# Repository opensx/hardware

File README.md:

# hardware
Design Files für die OpenSX Hardware, siehe <a href="http://opensx.net"> opensx.net </a>

Insgesamt soll mit den Projekten von "OpenSX" ein kompletter Modellbahnbetrieb möglich 
sein - die Bausteine können aber auch mit allen Standard Selectrix Modulen und Zentralen 
verwendet werden, sie sind "SX1-kompatibel".

Die Projekte auf diese Seite beruhen auf "Open Source" Software, aber auch auf 
"Open Source Hardware". Sie können also von jedem/jeder nachgebaut werden. 
Wir sind der Meinung, dass jeder/jeder die Möglichkeit haben sollte, die Hardware und 
auch die Software zu verstehen, sie ändern können sollte (und verbesssern) und auch 
diese Änderungen weitergeben sollte.

Dazu werden nach und nach nebem dem Source Code (lizensiert nach <a href="http://www.gnu.org/licenses/gpl-3.0.de.html">GPLv3</a>), 
der auch hier liegt, auch die Schaltpläne und Eagle Design Files veröffentlicht. 
Sie sind lizensiert unter der <a href="https://creativecommons.org/licenses/by-sa/4.0/de">"Creative Commons Attribution Share-Alike" Lizenz</a> - 
die eine persönliche und kommerzielle Weiterverwertung erlaubt, solange in angemesse Weise
die Urheberschaft von "opensx" erwähnt wird und die abgeleitete Arbeit unter der gleichen 
Lizenz steht. (dies ist die gleiche Lizenz wie beim Arduino Projekt)

<br />This work is licensed under a <a rel="license" href="http://creativecommons.org/licenses/by-sa/4.0/">Creative Commons Attribution-ShareAlike 4.0 International License</a>.

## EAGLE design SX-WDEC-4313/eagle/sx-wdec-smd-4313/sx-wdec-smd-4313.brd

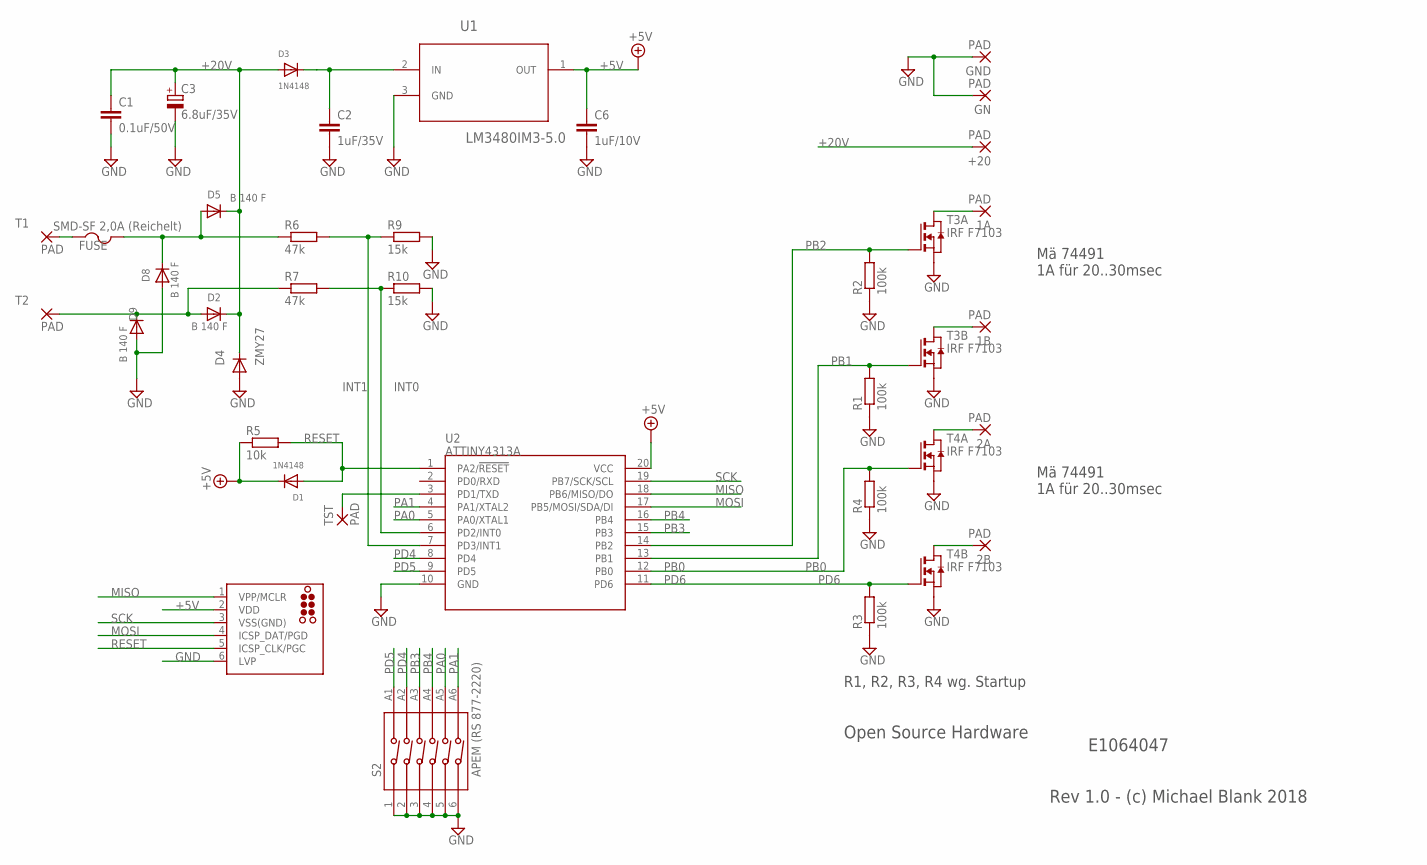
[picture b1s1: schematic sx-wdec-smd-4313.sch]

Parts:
1A, 1B, 2A, 2B: PAD; SMD1,27-2,54
+20: PAD; SMD1,27-2,54
C1: 0.1uF/50V; C0805
C2: 1uF/35V; C0805
C3: 6.8uF/35V; SMC_D
C6: 1uF/10V; C0805
D1, D3: 1N4148; SOD-323F
D2, D5, D8, D9: B 140 F; SMA-403D
D4: ZMY27; MELF-MLL41
FUSE: SMD-SF 2,0A (Reichelt); 1812
GN: PAD; SMD1,27-2,54
GND: PAD; SMD1,27-2,54
J1: ISP; TC2030-MCP-NL
R1, R2, R3, R4: 100k; R0805W
R5: 10k; R0805W
R6, R7: 47k; R0805W
R9, R10: 15k; R0805W
S2: APEM (RS 877-2220); 416131160806
T1, T2: PAD; SMD1,27-2,54
T3, T4: IRF F7103; SO8
TST: PAD; SMD1,27-2,54
U1: LM3480IM3-5.0; SOT95P263X110-3N
U2: ATTINY4313A; SOP20W

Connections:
+5V: C6.1, D1.C, J1.2 (VDD), R5.1, U1.1 (OUT), U2.20 (VCC)
+20V: +20.1, C1.1, C3.+, D2.C, D3.A, D4.C, D5.C
GND: C1.2, C2.2, C3.-, C6.2, D4.A, D8.A, D9.A, GN.1, GND.1, J1.6 (LVP), R1.1, R2.1, R3.1, R4.1, R9.2, R10.2, S2.1, S2.2, S2.3, S2.4, S2.5, S2.6, T3.1 (S), T3.3 (S), T4.1 (S), T4.3 (S), U1.3 (GND), U2.10 (GND)
INT0: R7.2, R10.1, U2.6 (PD2/INT0)
INT1: R6.2, R9.1, U2.7 (PD3/INT1)
MISO: J1.1 (VPP/MCLR), U2.18 (PB6/MISO/DO)
MOSI: J1.4 (ICSP_DAT/PGD), U2.17 (PB5/MOSI/SDA/DI)
unnamed: 2B.1, T4.5 (D), T4.6 (D)
unnamed: 2A.1, T4.7 (D), T4.8 (D)
unnamed: FUSE.1, T1.1
unnamed: D5.A, D8.C, FUSE.2, R6.1
unnamed: TST.1, U2.3 (PD1/TXD)
unnamed: C2.1, D3.C, U1.2 (IN)
unnamed: 1B.1, T3.5 (D), T3.6 (D)
unnamed: 1A.1, T3.7 (D), T3.8 (D)
PA0: S2.A5, U2.5 (PA0/XTAL1)
PA1: S2.A6, U2.4 (PA1/XTAL2)
PB0: R4.2, T4.2 (G), U2.12 (PB0)
PB1: R1.2, T3.4 (G), U2.13 (PB1)
PB2: R2.2, T3.2 (G), U2.14 (PB2)
PB3: S2.A3, U2.15 (PB3)
PB4: S2.A4, U2.16 (PB4)
PD4: S2.A2, U2.8 (PD4)
PD5: S2.A1, U2.9 (PD5)
PD6: R3.2, T4.4 (G), U2.11 (PD6)
RESET: D1.A, J1.5 (ICSP_CLK/PGC), R5.2, U2.1 (PA2/!RESET)
SCK: J1.3 (VSS(GND)), U2.19 (PB7/SCK/SCL)
TR-L: D2.A, D9.C, R7.1, T2.1

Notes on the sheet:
Mä 74491 1A für 20..30msec
R1, R2, R3, R4 wg. Startup
Open Source Hardware
Rev 1.0 - (c) Michael Blank 2018
E1064047

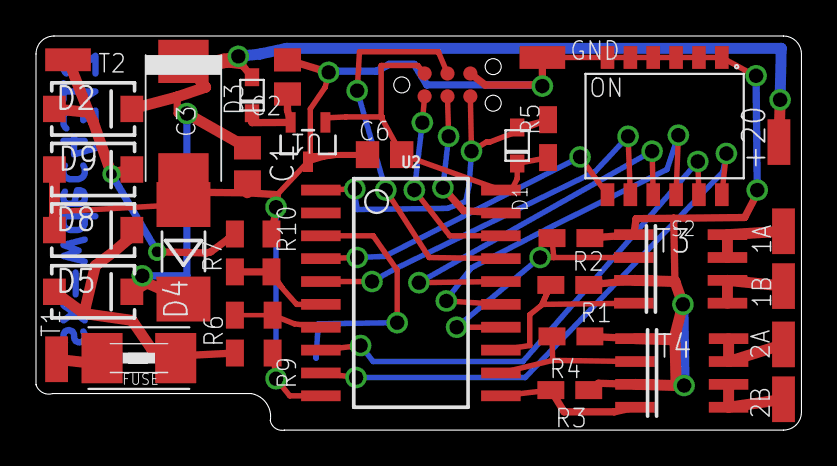
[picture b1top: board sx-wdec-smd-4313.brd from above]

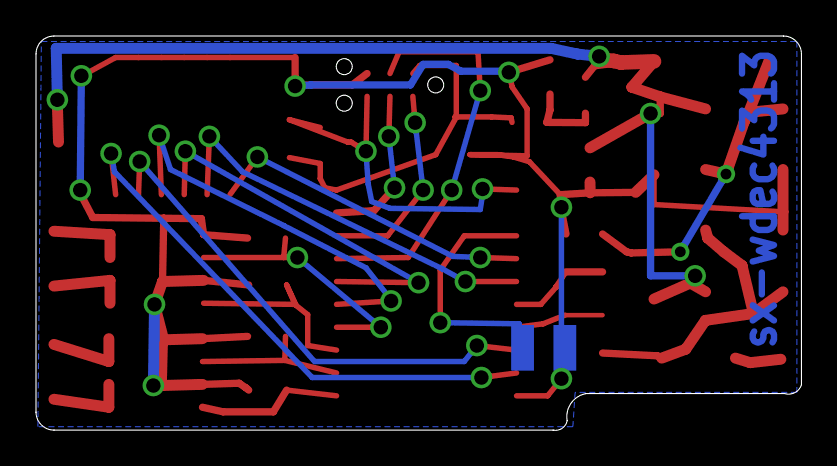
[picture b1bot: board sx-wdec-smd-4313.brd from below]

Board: 2 copper layers, 42.5 x 21.9 mm, 37 parts (2 on the bottom side), 28 nets.

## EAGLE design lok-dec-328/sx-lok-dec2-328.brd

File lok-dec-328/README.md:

# Arduino Lok-Decoder mit ATmega328
Design Files für die OpenSX Hardware, siehe <a href="http://opensx.net"> opensx.net </a>

Rev. 3, siehe sx-lok-dec3.sch.pdf : hier wurden 2 Widerstände an den Eingängen D2 und D3 nach Masse hinzugefügt - nur für Selectrix benötigt, da sonst die "0" Spannung nicht immer richtig erkannt wird.

lizensiert nach <a href="http://www.gnu.org/licenses/gpl-3.0.de.html">GPLv3</a>)

Sie sind lizensiert unter der <a href="https://creativecommons.org/licenses/by-sa/4.0/de">"Creative Commons Attribution Share-Alike" Lizenz</a> - 
die eine persönliche und kommerzielle Weiterverwertung erlaubt, solange in angemesse Weise
die Urheberschaft von "opensx" erwähnt wird und die abgeleitete Arbeit unter der gleichen 
Lizenz steht. (dies ist die gleiche Lizenz wie beim Arduino Projekt)

<br />This work is licensed under a <a rel="license" href="http://creativecommons.org/licenses/by-sa/4.0/">Creative Commons Attribution-ShareAlike 4.0 International License</a>.

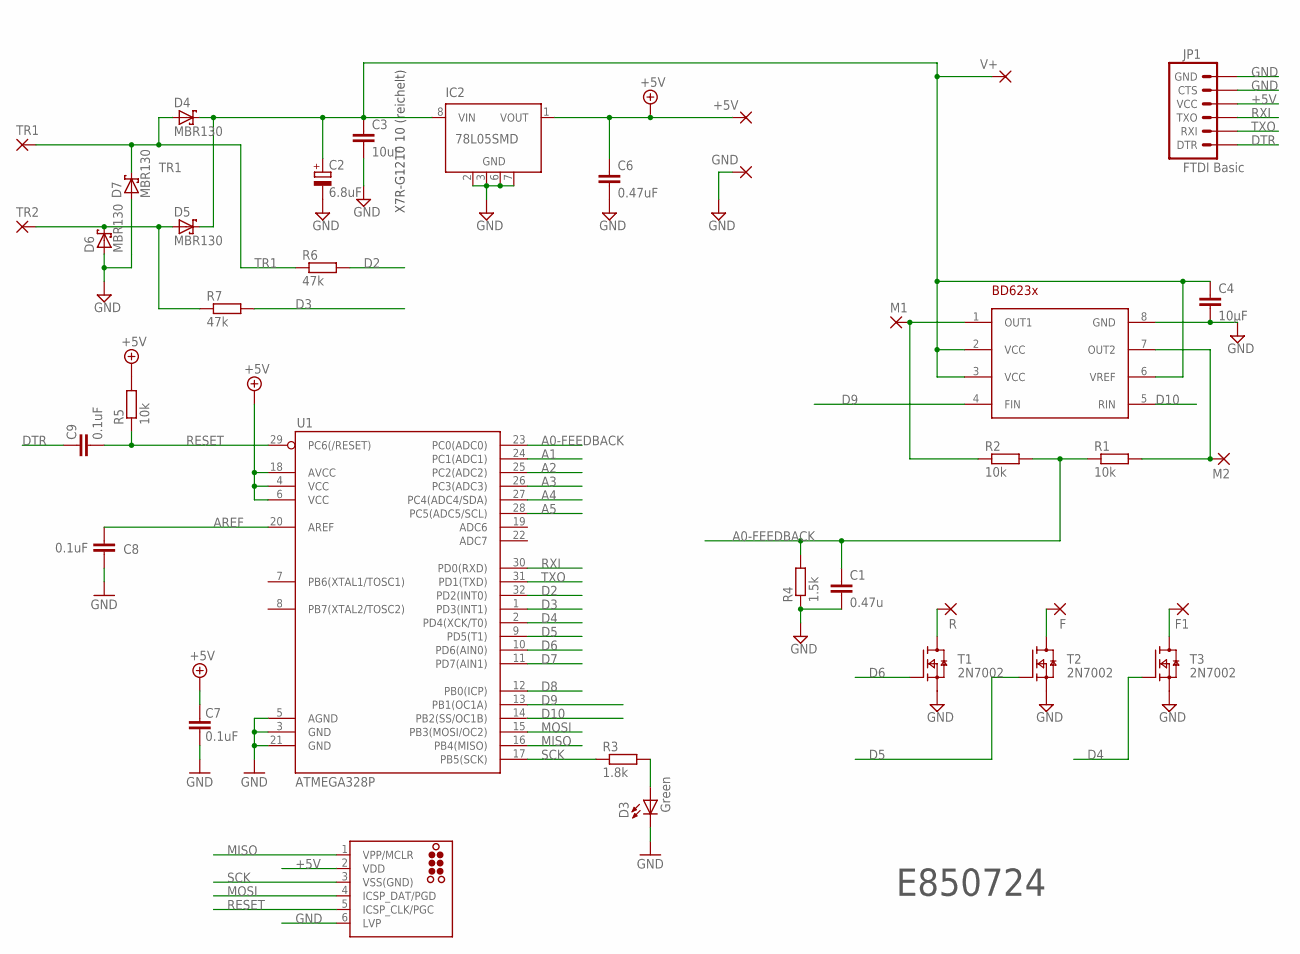
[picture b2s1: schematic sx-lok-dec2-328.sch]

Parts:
+5V: SMD2; SMD1,27-2,54
BD6231: BD6231F; SOP8
C1: 0.47u; C1206
C2: 6.8uF; SMC_D
C3: 10uF; C0805K
C4: 10µF; C1210K
C6: 0.47uF; C1206
C7, C8, C9: 0.1uF; 0805
D3: Green; LED-0603
D4, D5, D6, D7: MBR130; SOD123F
F, F1: SMD2; SMD1,27-2,54
GND: SMD2; SMD1,27-2,54
IC2: 78L05SMD; SO08
J1: ISP; TC2030-MCP-NL
JP1: FTDI Basic; 1X06
M1, M2: SMD2; SMD1,27-2,54
R: SMD2; SMD1,27-2,54
R1, R2: 10k; R0805
R3: 1.8k; M0805
R4: 1.5k; R0805
R5: 10k; M0805
R6: 47k; R0805
R7: 47k; M0805
T1, T2, T3: 2N7002; SOT23
TR1, TR2: SMD2; SMD1,27-2,54
U1: ATMEGA328P; TQFP32-08
V+: SMD2; SMD1,27-2,54

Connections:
+5V: +5V.1, C6.1, C7.2, IC2.1 (VOUT), J1.2 (VDD), JP1.4 (VCC), R5.2, U1.4 (VCC), U1.6 (VCC), U1.18 (AVCC)
+20V: BD6231.2 (VCC), BD6231.3 (VCC), BD6231.6 (VREF), C2.+, C3.1, C4.1, D4.1 (K), D5.1 (K), IC2.8 (VIN), V+.1
A0-FEEDBACK: C1.1, R1.1, R2.2, R4.2, U1.23 (PC0(ADC0))
A1: U1.24 (PC1(ADC1))
A2: U1.25 (PC2(ADC2))
A3: U1.26 (PC3(ADC3))
A4: U1.27 (PC4(ADC4/SDA))
A5: U1.28 (PC5(ADC5/SCL))
AREF: C8.2, U1.20 (AREF)
D2: R6.2, U1.32 (PD2(INT0))
D3: R7.2, U1.1 (PD3(INT1))
D4: T3.1 (G), U1.2 (PD4(XCK/T0))
D5: T2.1 (G), U1.9 (PD5(T1))
D6: T1.1 (G), U1.10 (PD6(AIN0))
D7: U1.11 (PD7(AIN1))
D8: U1.12 (PB0(ICP))
D9: BD6231.4 (FIN), U1.13 (PB1(OC1A))
D10: BD6231.5 (RIN), U1.14 (PB2(SS/OC1B))
DTR: C9.2, JP1.1 (DTR)
GND: BD6231.8 (GND), C1.2, C2.-, C3.2, C4.2, C6.2, C7.1, C8.1, D3.C, D6.2 (A), D7.2 (A), GND.1, IC2.2 (GND), IC2.3 (GND), IC2.6 (GND), IC2.7 (GND), J1.6 (LVP), JP1.5 (CTS), JP1.6 (GND), R4.1, T1.2 (S), T2.2 (S), T3.2 (S), U1.3 (GND), U1.5 (AGND), U1.21 (GND)
MISO: J1.1 (VPP/MCLR), U1.16 (PB4(MISO))
MOSI: J1.4 (ICSP_DAT/PGD), U1.15 (PB3(MOSI/OC2))
MOTOR1: BD6231.1 (OUT1), M1.1, R2.1
MOTOR2: BD6231.7 (OUT2), M2.1, R1.2
unnamed: D3.A, R3.2
unnamed: R.1, T1.3 (D)
unnamed: F.1, T2.3 (D)
unnamed: F1.1, T3.3 (D)
RESET: C9.1, J1.5 (ICSP_CLK/PGC), R5.1, U1.29 (PC6(/RESET))
RXI: JP1.3 (TXO), U1.30 (PD0(RXD))
SCK: J1.3 (VSS(GND)), R3.1, U1.17 (PB5(SCK))
TR1: D4.2 (A), D7.1 (K), R6.1, TR1.1
TR-L1: D5.2 (A), D6.1 (K), R7.1, TR2.1
TXO: JP1.2 (RXI), U1.31 (PD1(TXD))

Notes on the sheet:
X7R-G1210 10 (reichelt)
E850724

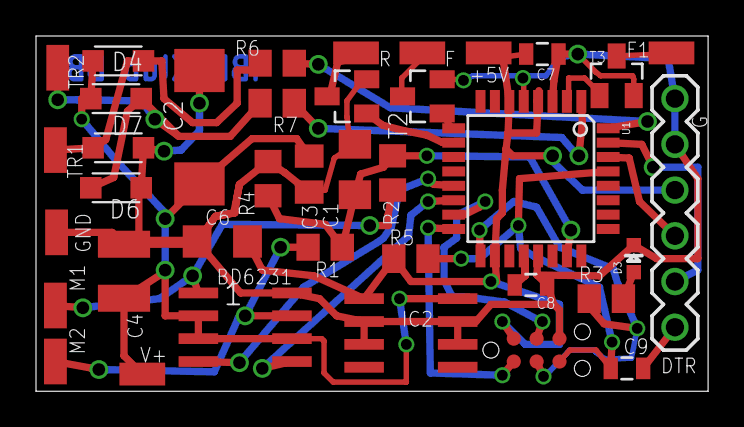
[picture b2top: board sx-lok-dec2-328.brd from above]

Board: 2 copper layers, 37.3 x 19.7 mm, 38 parts (0 on the bottom side), 27 nets.

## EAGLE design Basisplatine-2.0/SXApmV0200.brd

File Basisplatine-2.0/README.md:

# Basisplatine 2.0 mit DIN Buchsen

siehe <a href="http://opensx.net/projekte/basisplatine/neue-version-v02-00/"> OpenSX Basisplatine Version 2.00 mit DIN Buchsen</a> - hierzu muss die Arduino Lib SX30 verwendet werden, siehe  <a href="https://github.com/opensx/SX30/"> SX Library mit Beispiel "Belegtmelder" </a>.

Auf die Basisplatine kann zB eine Belegtmelderplatine aufgesetzt werden:

<br />This work is licensed under a <a rel="license" href="http://creativecommons.org/licenses/by-sa/4.0/">Creative Commons Attribution-ShareAlike 4.0 International License</a>.

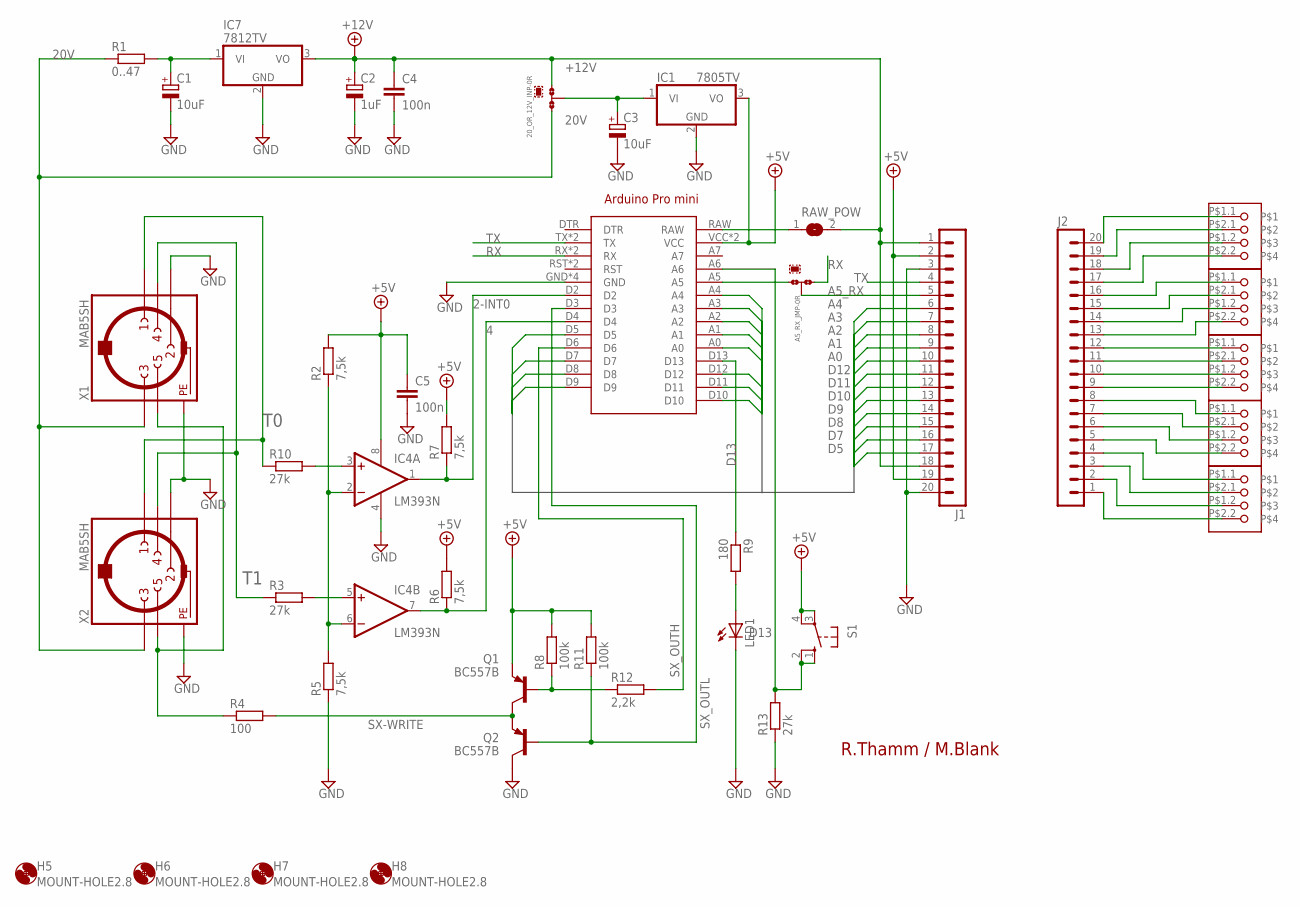
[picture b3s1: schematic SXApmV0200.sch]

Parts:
20_OR_12V_INP: 0R-JUMPA; A0R-JMP
A5_RX_JMP: 0R-JUMPB; B0R-JMP
ARDUINO1: ARDUINO_PRO_MINI
C1: 10uF; E2,5-7
C2: 1uF; E2,5-7
C3: 10uF; SMC_C
C4, C5: 100n; C050-025X075
H5, H6, H7, H8: MOUNT-HOLE2.8; 2,8
IC1: 7805TV; TO220V
IC4: LM393N; DIL08
IC7: 7812TV; TO220V
J1, J2: MA20-1
LED1: LED3MM
Q1, Q2: BC557B; TO92-EBC
R1: 0..47; 0207/12
R2, R5, R6, R7: 7,5k; 0207/10
R3, R10, R13: 27k; 0207/10
R4: 100; 0207/10
R8, R11: 100k; 0207/10
R9: 180; 0207/2V
R12: 2,2k; 0207/10
RAW_POW: SJ
S1: 10-XX; B3F-10XX
U$1, U$2, U$3, U$4, U$5: AKL093-06
X1, X2: MAB5SH

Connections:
2-INT0: ARDUINO1.D2, IC4.1 (OUT), R7.1
4: ARDUINO1.D4, IC4.7 (OUT), R6.1
20V: 20_OR_12V_INP.3, R1.1, X1.3, X2.3
+5V: ARDUINO1.VCC, ARDUINO1.VCC@1 (VCC), C5.1, IC1.3 (VO), IC4.8 (V+), J1.2, J1.19, Q1.E, R2.2, R6.2, R7.2, R8.2, R11.2, S1.3, S1.4 (P1)
+12V: 20_OR_12V_INP.1, C2.+, C4.1, IC7.3 (VO), J1.1, J1.18, RAW_POW.2
A0: ARDUINO1.A0, J1.10
A1: ARDUINO1.A1, J1.9
A2: ARDUINO1.A2, J1.8
A3: ARDUINO1.A3, J1.7
A4: ARDUINO1.A4, J1.6
A5: A5_RX_JMP.3, ARDUINO1.A5
A5_RX: A5_RX_JMP.2, J1.5
D5: ARDUINO1.D5, J1.17
D7: ARDUINO1.D7, J1.16
D8: ARDUINO1.D8, J1.15
D9: ARDUINO1.D9, J1.14
D10: ARDUINO1.D10, J1.13
D11: ARDUINO1.D11, J1.12
D12: ARDUINO1.D12, J1.11
D13: ARDUINO1.D13, R9.1
GND: ARDUINO1.GND, ARDUINO1.GND@1 (GND), ARDUINO1.GND@2 (GND), ARDUINO1.GND@3 (GND), C1.-, C2.-, C3.-, C4.2, C5.2, IC1.2 (GND), IC4.4 (V-), IC7.2 (GND), J1.3, J1.20, LED1.K (C), Q2.C, R5.1, R13.1, X1.2, X1.PE, X1.PE@ (PE), X1.PE@1 (PE), X1.PE@2 (PE), X2.2, X2.PE, X2.PE@ (PE), X2.PE@1 (PE), X2.PE@2 (PE)
unnamed: LED1.A, R9.2
unnamed: C1.+, IC7.1 (VI), R1.2
unnamed: R4.1, X1.5, X2.5
unnamed: IC4.3 (+IN), R10.2
unnamed: IC4.5 (+IN), R3.2
unnamed: J2.1, U$4.P$2.2
unnamed: IC4.2 (-IN), IC4.6 (-IN), R2.1, R5.2
unnamed: J2.2, U$4.P$1.2
unnamed: J2.3, U$4.P$2.1
unnamed: J2.4, U$4.P$1.1
unnamed: J2.5, U$3.P$2.2
unnamed: J2.6, U$3.P$1.2
unnamed: J2.7, U$3.P$2.1
unnamed: J2.8, U$3.P$1.1
unnamed: J2.9, U$1.P$2.2
unnamed: J2.10, U$1.P$1.2
unnamed: J2.11, U$1.P$2.1
unnamed: J2.12, U$1.P$1.1
unnamed: J2.13, U$2.P$2.2
unnamed: J2.14, U$2.P$1.2
unnamed: J2.15, U$2.P$2.1
unnamed: J2.16, U$2.P$1.1
unnamed: J2.17, U$5.P$2.2
unnamed: J2.18, U$5.P$1.2
unnamed: J2.19, U$5.P$2.1
unnamed: J2.20, U$5.P$1.1
unnamed: ARDUINO1.A6, R13.2, S1.1 (S), S1.2 (S1)
unnamed: Q1.B, R8.1, R12.1
unnamed: ARDUINO1.RAW, RAW_POW.1
unnamed: 20_OR_12V_INP.2, C3.+, IC1.1 (VI)
RX: A5_RX_JMP.1, ARDUINO1.RX, ARDUINO1.RX@1 (RX)
SX-WRITE: Q1.C, Q2.E, R4.2
SX_OUTH: ARDUINO1.D6, R12.2
SX_OUTL: ARDUINO1.D3, Q2.B, R11.1
T0: R10.1, X1.1, X2.1
T1: R3.1, X1.4, X2.4
TX: ARDUINO1.TX, ARDUINO1.TX@1 (TX), J1.4

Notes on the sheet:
R.Thamm / M.Blank

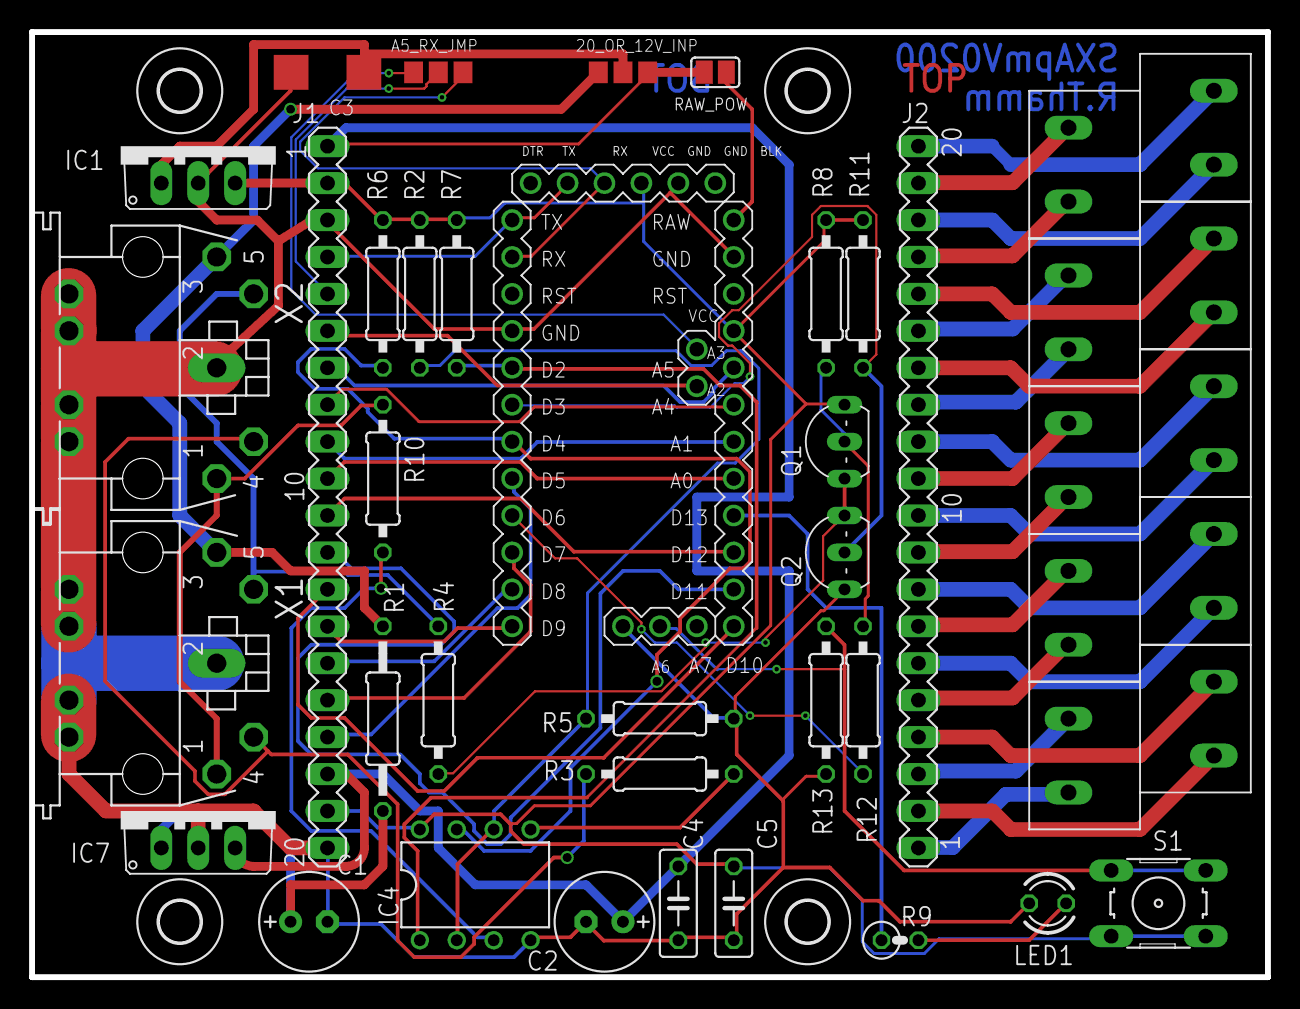
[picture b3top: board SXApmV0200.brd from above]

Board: 2 copper layers, 85.0 x 65.0 mm, 42 parts (0 on the bottom side), 58 nets.

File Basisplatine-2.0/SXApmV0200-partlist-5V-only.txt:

Partlist

Exported from SXApmV0200.sch at 16.09.16 17:11

Assembly variant: 5V-only !

Part           Value          Package          

20_OR_12V_INP  Jumper in Stellung "20" (der 5V Regler wird direkt aus den 20V vom Bus gespeist)
A5_RX_JMP      nicht gesetzt (=offen)
ARDUINO1       ARDUINO_PRO_MINI (5V Version)
C1             nicht bestückt
C2             nicht bestückt
C3             10uF / 35V (nicht notwendig, wenn 5V Schaltregler verwendet wird)
C4             nicht bestückt
C5             100n (Keramik Cap.)  
IC1            TSR 0.5-2450 (Reichelt, Traco, 5V Schaltregler, 500mA)       
IC4            LM393N         DIL08                    
IC7            nicht bestückt !           
J1             MA20-1        Buchsenleiste 20 polig, 2.54mm Raster, 8.5mm hoch
                             (zum Beispiel Reichelt BL 1X20G8 2,54 )
J2             MA20-1        Buchsenleiste 20 polig, 2.54mm Raster, 8.5mm hoch
LED1           LED3MM        (rot oder grün)
Q1             BC557B         TO92-EBC         transistor-pnp     
Q2             BC557B         TO92-EBC         transistor-pnp    
R1             nicht bestückt
R2             7,5k           R-EU_0207/10     
R3             27k            R-EU_0207/10     
R4             100            R-EU_0207/10     
R5             7,5k           R-EU_0207/10     
R6             7,5k           R-EU_0207/10     
R7             7,5k           R-EU_0207/10     
R8             100k           R-EU_0207/10     
R9             180 (bzw 1.8k, wenn die LED1 vom Typ "low current" (2mA) ist)       
R10            27k            R-EU_0207/10     
R11            100k           R-EU_0207/10     
R12            2,2k           R-EU_0207/10     
R13            27k            R-EU_0207/10     
RAW_POW        nicht gesetzt (=offen)           1
S1             Kurzhubtaster 6x6mm (z.B. Reichelt TASTER 3301)
U$1..U$5       Nur die vorderen 10 Kontakte werden genutzt (RM 5,08)
                      (zum Beispiel Reichelt - AKL 101-10)
X1             DIN-Buchse, 5polig (zB Reichelt MABP 5S oder Reichelt MABPM 5S )
X2             DIN-Buchse, 5polig (zB Reichelt MABP 5S oder Reichelt MABPM 5S )

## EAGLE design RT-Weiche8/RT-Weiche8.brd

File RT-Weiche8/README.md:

# "RT-Weiche8" Add-on Platine (für eine der SX- oder LocoNet- Basisplatinen) 

Sie ermöglicht das Ansteuern von 8 Tortoise Antrieben (mit LB1909MC Treibern).

Für die Weichenmotoren ist eine separate Spannung vorgesehen (IC1), sie kann zum Beispiel 9V oder 12V betragen.

Modul-Gehäuse: Strapubox 523 (strapubox.de)

<br />This work is licensed under a <a rel="license" href="http://creativecommons.org/licenses/by-sa/4.0/">Creative Commons Attribution-ShareAlike 4.0 International License</a>.

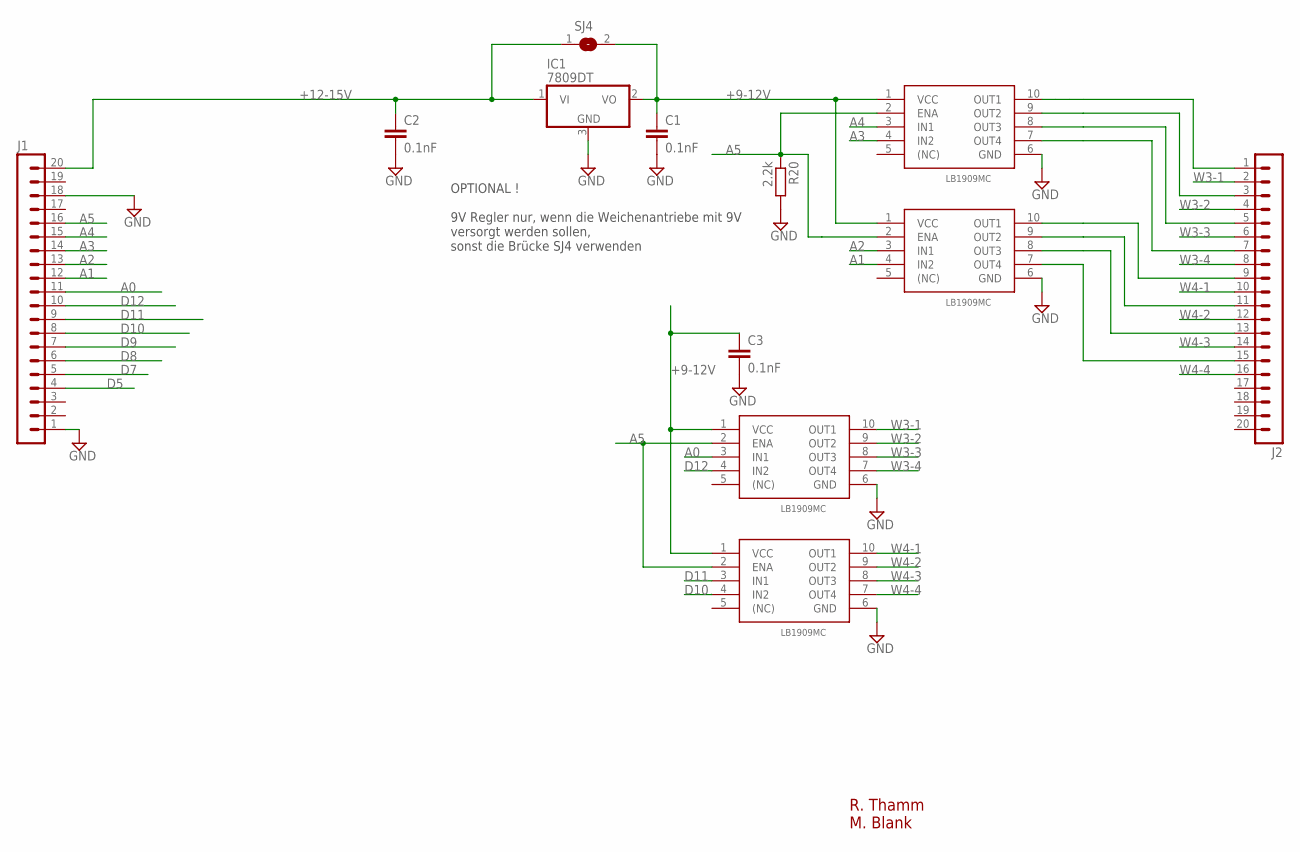
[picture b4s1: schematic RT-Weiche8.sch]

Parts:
C1, C2, C3: 0.1nF; C0805K
IC1: 7809DT; TO252
J1, J2: MA20-1
LB1909-1, LB1909-2, LB1909-3, LB1909-4: LB1909MC; MSOIC10-1MM
R20: 2.2k; R0805W
SJ4: SJ

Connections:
+9-12V: C1.1, C3.1, IC1.2 (VO), LB1909-1.1 (VCC), LB1909-2.1 (VCC), LB1909-3.1 (VCC), LB1909-4.1 (VCC), SJ4.2
+12-15V: C2.1, IC1.1 (VI), J1.20, SJ4.1
A0: J1.11, LB1909-3.3 (IN1)
A1: J1.12, LB1909-2.4 (IN2)
A2: J1.13, LB1909-2.3 (IN1)
A3: J1.14, LB1909-1.4 (IN2)
A4: J1.15, LB1909-1.3 (IN1)
A5: J1.16, LB1909-1.2 (ENA), LB1909-2.2 (ENA), LB1909-3.2 (ENA), LB1909-4.2 (ENA), R20.1
D5: J1.4
D7: J1.5
D8: J1.6
D9: J1.7
D10: J1.8, LB1909-4.4 (IN2)
D11: J1.9, LB1909-4.3 (IN1)
D12: J1.10, LB1909-3.4 (IN2)
GND: C1.2, C2.2, C3.2, IC1.3 (GND), J1.1, J1.18, LB1909-1.6 (GND), LB1909-2.6 (GND), LB1909-3.6 (GND), LB1909-4.6 (GND), R20.2
unnamed: J2.9, LB1909-2.10 (OUT1)
unnamed: J2.13, LB1909-2.8 (OUT3)
unnamed: J2.1, LB1909-1.10 (OUT1)
unnamed: J2.15, LB1909-2.7 (OUT4)
unnamed: J2.3, LB1909-1.9 (OUT2)
unnamed: J2.5, LB1909-1.8 (OUT3)
unnamed: J2.7, LB1909-1.7 (OUT4)
unnamed: J2.11, LB1909-2.9 (OUT2)
W3-1: J2.2, LB1909-3.10 (OUT1)
W3-2: J2.4, LB1909-3.9 (OUT2)
W3-3: J2.6, LB1909-3.8 (OUT3)
W3-4: J2.8, LB1909-3.7 (OUT4)
W4-1: J2.10, LB1909-4.10 (OUT1)
W4-2: J2.12, LB1909-4.9 (OUT2)
W4-3: J2.14, LB1909-4.8 (OUT3)
W4-4: J2.16, LB1909-4.7 (OUT4)

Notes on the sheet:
R. Thamm M. Blank
OPTIONAL ! 9V Regler nur, wenn die Weichenantriebe mit 9V versorgt werden sollen, sonst die Brücke SJ4 verwenden

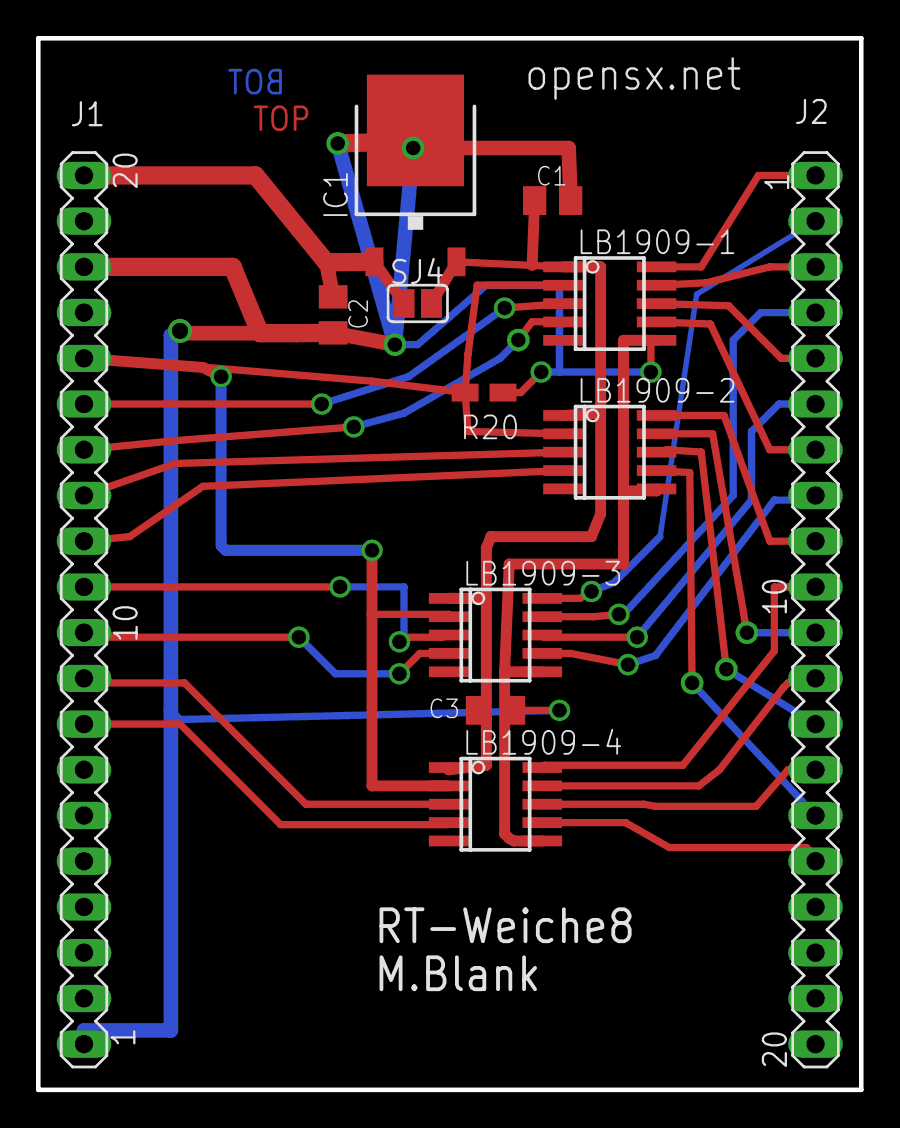
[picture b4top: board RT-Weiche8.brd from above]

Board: 2 copper layers, 45.7 x 58.4 mm, 12 parts (0 on the bottom side), 28 nets.

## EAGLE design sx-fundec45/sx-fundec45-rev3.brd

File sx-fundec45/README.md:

# Funktionsdekoder für Selectrix mit ATtiny45

mehr dazu unter <a href="http://opensx.net/projekte/funktionsdekoder/sx-fundec45"> OpenSX.net - Projekt "funcdec45"</a> 

<br />This work is licensed under a <a rel="license" href="http://creativecommons.org/licenses/by-sa/4.0/">Creative Commons Attribution-ShareAlike 4.0 International License</a>.

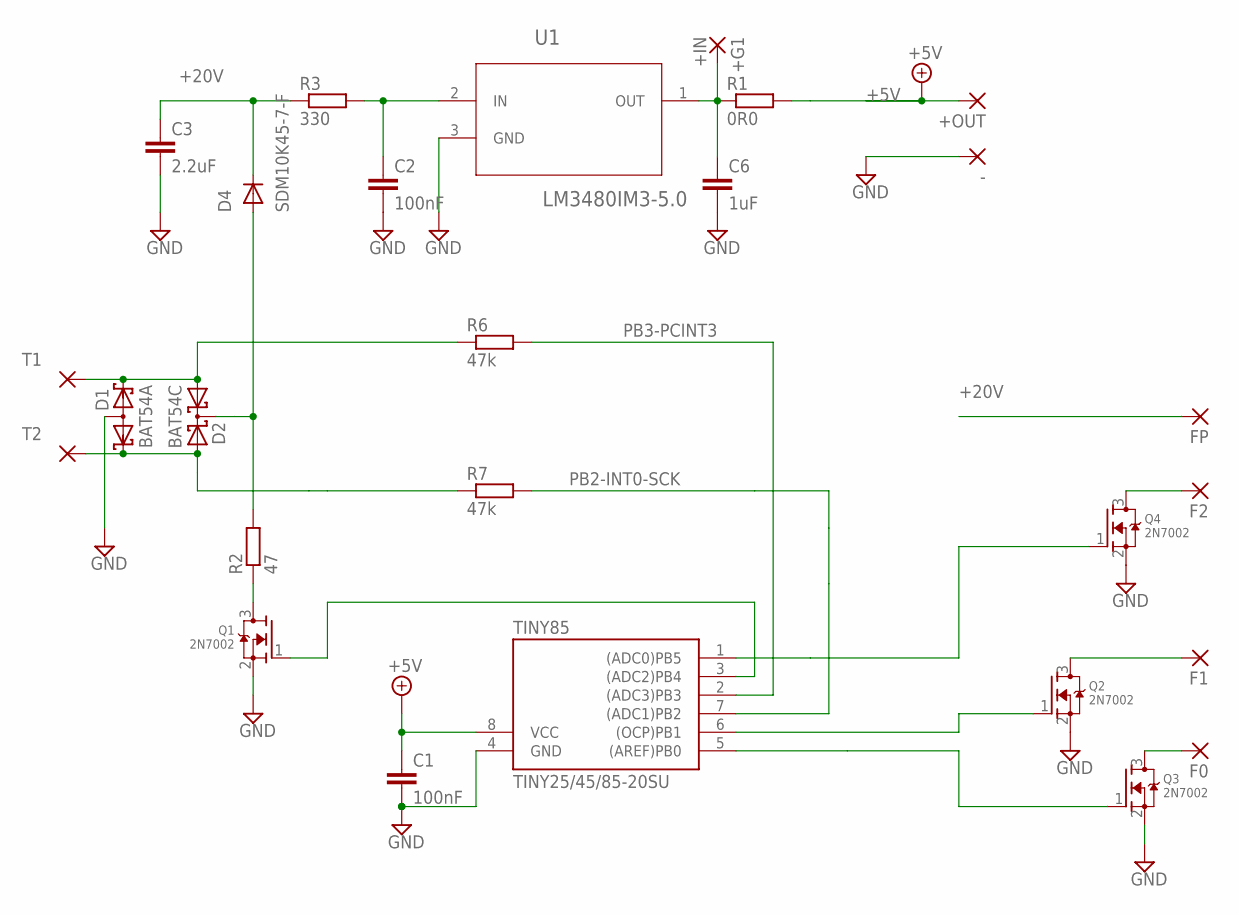
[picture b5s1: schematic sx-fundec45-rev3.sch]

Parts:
+G1: +IN; SMD1,27-2,54
+OUT: SMD2; SMD1,27-2,54
-: SMD2; SMD1,27-2,54
C1, C2: 100nF; C0805
C3: 2.2uF; C1206
C6: 1uF; C0805
D1: BAT54A; SOT23
D2: BAT54C; SOT23
D4: SDM10K45-7-F; SOD323-R
F0, F1, F2: SMD2; SMD1,27-2,54
FP: SMD2; SMD1,27-2,54
Q1, Q2, Q3, Q4: 2N7002; SOT23
R1: 0R0; M0805
R2: 47; R0805
R3: 330; M0805
R6: 47k; R0805
R7: 47k; M0805
T1, T2: SMD2; SMD1,27-2,54
TINY85: TINY25/45/85-20SU; SOIC8
U1: LM3480IM3-5.0; SOT95P263X110-3N

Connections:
+5V: +OUT.1, C1.1, R1.2, TINY85.8 (VCC)
+20V: C3.1, D4.C, FP.1, R3.1
+IN: +G1.1, C6.1, R1.1, U1.1 (OUT)
F2: Q4.1 (G), TINY85.1 ((ADC0)PB5)
GND: -.1, C1.2, C2.2, C3.2, C6.2, D1.3 (AA), Q1.2 (S), Q2.2 (S), Q3.2 (S), Q4.2 (S), TINY85.4 (GND), U1.3 (GND)
MISO: Q2.1 (G), TINY85.6 ((OCP)PB1)
MOSI: Q3.1 (G), TINY85.5 ((AREF)PB0)
unnamed: D2.3 (CC), D4.A, R2.2
unnamed: Q1.3 (D), R2.1
unnamed: Q1.1 (G), TINY85.3 ((ADC2)PB4)
unnamed: D1.2 (K2), D2.1 (A1), R6.1, T1.1
unnamed: C2.1, R3.2, U1.2 (IN)
unnamed: F1.1, Q2.3 (D)
unnamed: F0.1, Q3.3 (D)
unnamed: F2.1, Q4.3 (D)
PB2-INT0-SCK: R7.2, TINY85.7 ((ADC1)PB2)
PB3-PCINT3: R6.2, TINY85.2 ((ADC3)PB3)
TR-L: D1.1 (K1), D2.2 (A2), R7.1, T2.1

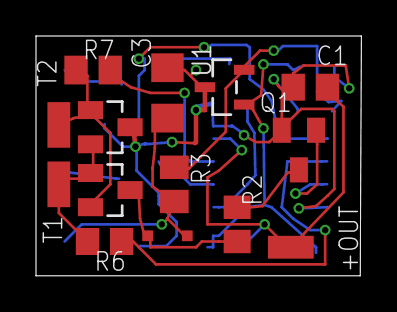
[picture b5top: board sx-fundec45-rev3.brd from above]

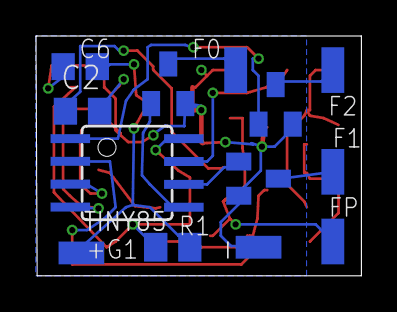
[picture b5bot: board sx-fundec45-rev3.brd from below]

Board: 2 copper layers, 18.1 x 13.3 mm, 27 parts (13 on the bottom side), 18 nets.

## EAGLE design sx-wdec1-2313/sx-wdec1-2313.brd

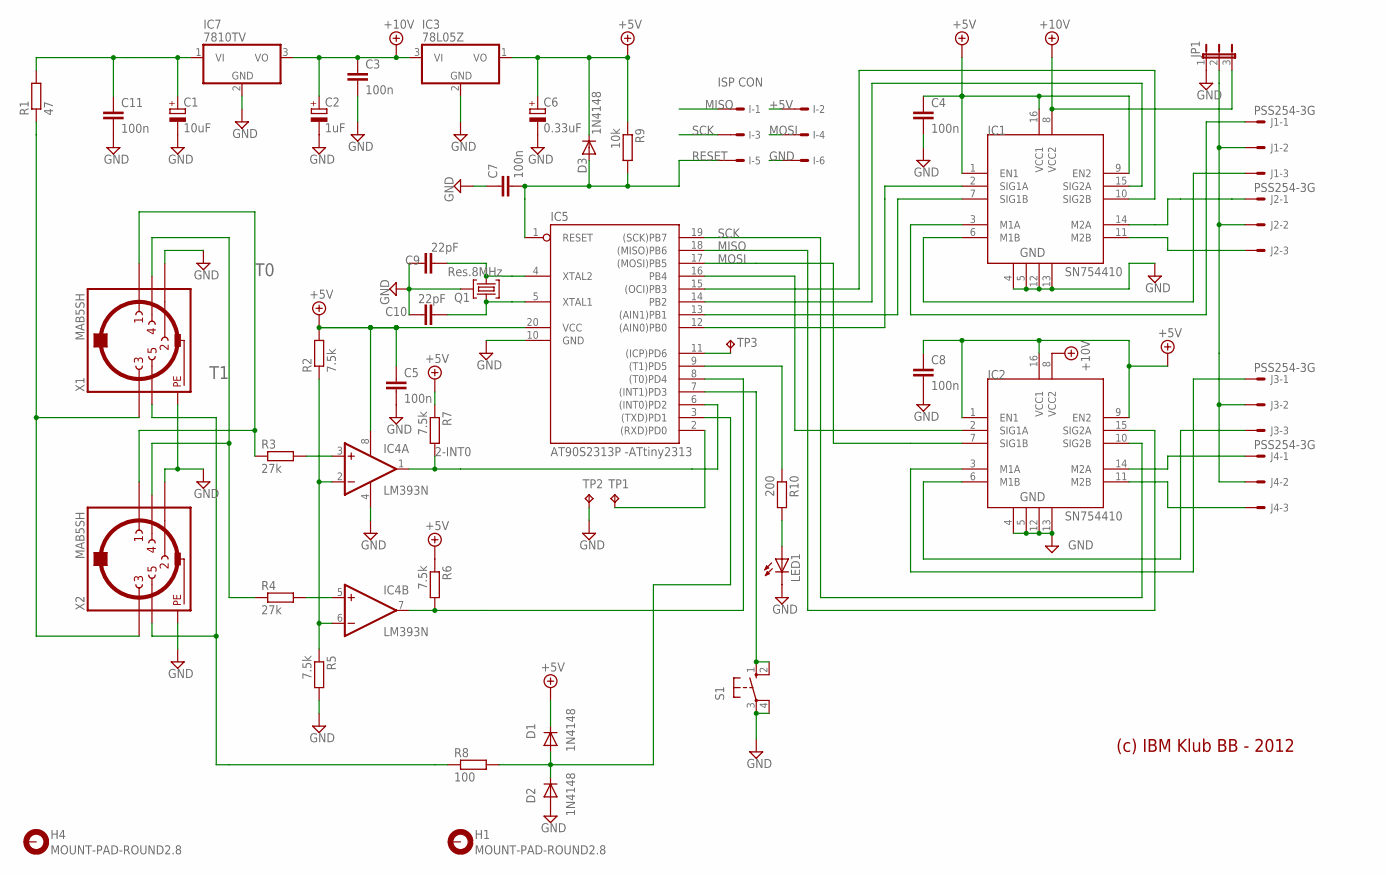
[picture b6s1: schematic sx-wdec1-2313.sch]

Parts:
C1: 10uF; E2,5-7
C2: 1uF; E2,5-7
C3, C4, C5, C7, C8, C11: 100n; C050-025X075
C6: 0.33uF; E2,5-5
C9, C10: 22pF; C025-025X050
D1, D2, D3: 1N4148; DO35-7
H1, H4: MOUNT-PAD-ROUND2.8; 2,8-PAD
I: ISP CON; 057-006-1
IC1, IC2: SN754410; DIP16
IC3: 78L05Z; TO92
IC4: LM393N; DIL08
IC5: AT90S2313P -ATtiny2313; DIL20
IC7: 7810TV; TO220V
J1, J2, J3, J4: PSS254-3G; 6410-03
JP1: JP2E; JP2
LED1: LED3MM
Q1: Res.8MHz; HC49U
R1: 47; 0207/12
R2, R5, R6, R7: 7.5k; 0207/10
R3, R4: 27k; 0207/10
R8: 100; 0207/10
R9: 10k; 0207/10
R10: 200; 0207/10
S1: 10-XX; B3F-10XX
TP1, TP2, TP3: TPPAD1-13; P1-13
X1, X2: MAB5SH

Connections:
2-INT0: IC4.1 (OUT), IC5.6 ((INT0)PD2), R7.2
4: IC4.7 (OUT), IC5.8 ((T0)PD4), R6.2
6: IC1.15 (SIG2A), IC5.14 (PB2)
9: IC1.10 (SIG2B), IC5.15 ((OCI)PB3)
10: IC2.2 (SIG1A), IC5.16 (PB4)
+5V: C4.1, C5.1, C6.+, C8.1, D1.C, D3.C, I.2, IC1.1 (EN1), IC1.9 (EN2), IC1.16 (VCC1), IC2.1 (EN1), IC2.9 (EN2), IC2.16 (VCC1), IC3.1 (VO), IC4.8 (V+), IC5.20 (VCC), R2.2, R6.1, R7.1, R9.1
+10V: C2.+, C3.1, IC1.8 (VCC2), IC2.8 (VCC2), IC3.3 (VI), IC7.3 (VO), JP1.3
GND: C1.-, C2.-, C3.2, C4.2, C5.2, C6.-, C7.1, C8.2, C9.1, C10.1, C11.2, D2.A, I.6, IC1.4, IC1.5, IC1.12, IC1.13, IC2.4, IC2.5, IC2.12, IC2.13, IC3.2 (GND), IC4.4 (V-), IC5.10 (GND), IC7.2 (GND), JP1.1, LED1.K (C), Q1.2, R5.2, S1.3, S1.4 (P1), TP2.TP, X1.2, X1.PE, X1.PE@ (PE), X2.2, X2.PE, X2.PE@ (PE)
MISO: I.1, IC2.15 (SIG2A), IC5.18 ((MISO)PB6)
MOSI: I.4, IC2.7 (SIG1B), IC5.17 ((MOSI)PB5)
unnamed: R1.1, X1.3, X2.3
unnamed: C1.+, C11.1, IC7.1 (VI), R1.2
unnamed: R8.1, X1.5, X2.5
unnamed: IC4.3 (+IN), R3.2
unnamed: IC4.5 (+IN), R4.2
unnamed: D1.A, D2.C, IC5.3 ((TXD)PD1), R8.2
unnamed: IC4.2 (-IN), IC4.6 (-IN), R2.1, R5.1
unnamed: IC1.2 (SIG1A), IC5.12 ((AIN0)PB0)
unnamed: IC1.3 (M1A), J1.1
unnamed: IC1.6 (M1B), J1.3
unnamed: IC1.14 (M2A), J2.1
unnamed: IC1.11 (M2B), J2.3
unnamed: IC2.3 (M1A), J3.1
unnamed: IC2.6 (M1B), J3.3
unnamed: IC2.14 (M2A), J4.1
unnamed: IC2.11 (M2B), J4.3
unnamed: C9.2, IC5.4 (XTAL2), Q1.1
unnamed: C10.2, IC5.5 (XTAL1), Q1.3
unnamed: IC1.7 (SIG1B), IC5.13 ((AIN1)PB1)
unnamed: IC5.2 ((RXD)PD0), TP1.TP
unnamed: IC5.7 ((INT1)PD3), S1.1 (S), S1.2 (S1)
unnamed: J1.2, J2.2, J3.2, J4.2, JP1.2
unnamed: IC5.9 ((T1)PD5), R10.1
unnamed: LED1.A, R10.2
unnamed: IC5.11 ((ICP)PD6), TP3.TP
RESET: C7.2, D3.A, I.5, IC5.1 (RESET), R9.2
SCK: I.3, IC2.10 (SIG2B), IC5.19 ((SCK)PB7)
T0: R3.1, X1.1, X2.1
T1: R4.1, X1.4, X2.4

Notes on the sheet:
(c) IBM Klub BB - 2012

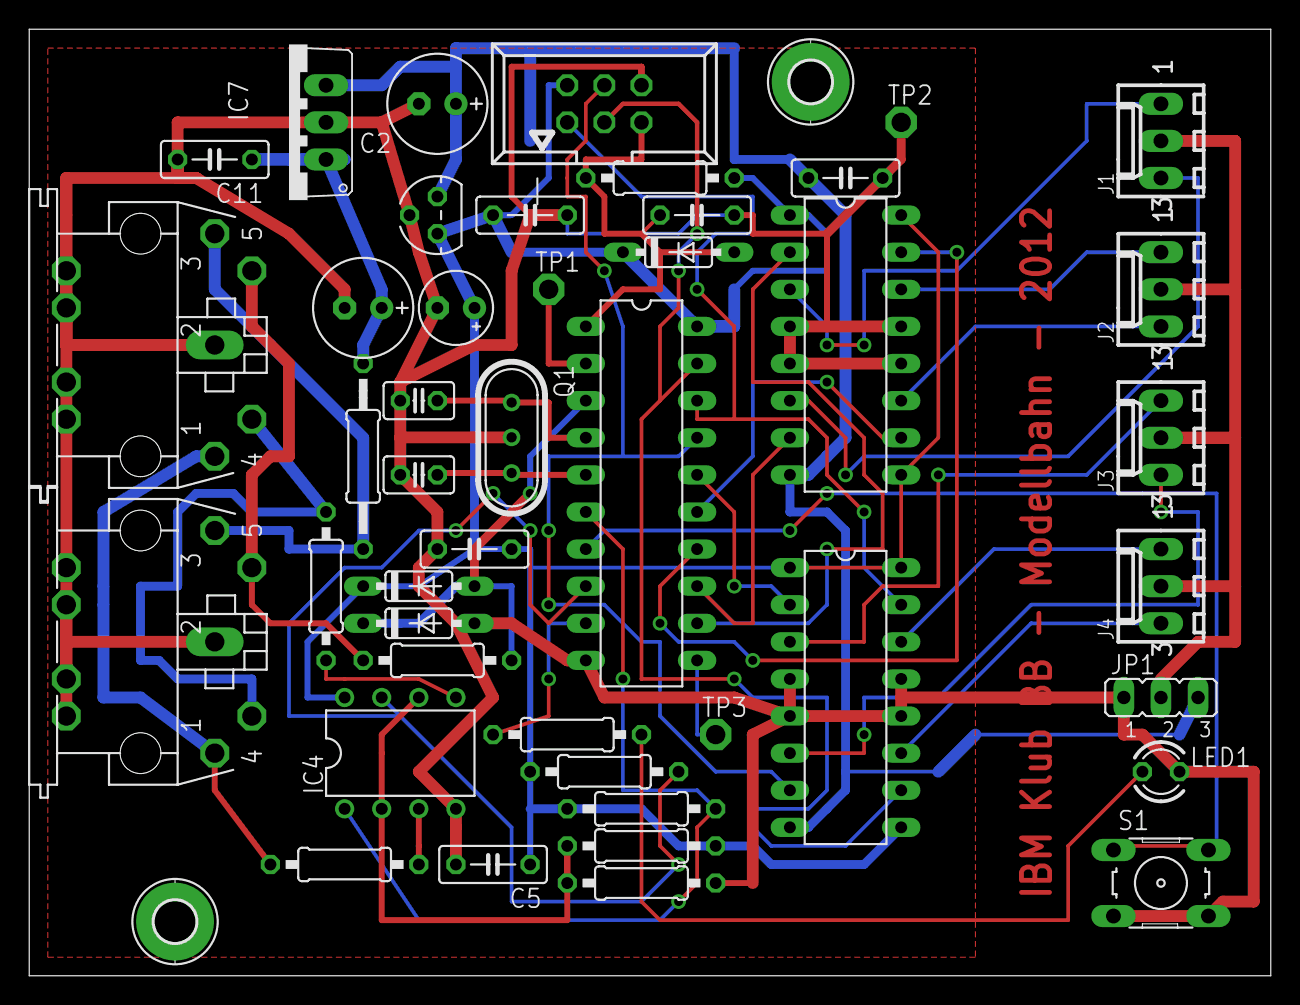
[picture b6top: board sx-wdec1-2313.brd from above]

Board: 2 copper layers, 85.0 x 64.8 mm, 46 parts (0 on the bottom side), 39 nets.

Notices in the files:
parts and their libraries:
tag-connect: ©2009 ROFA.cz - modified and updated by Robert Darlington ‹rdarlington@gmail.com›
Switches_rev15f: Copyright: Würth Elektronik
SparkFun-IC-Microcontroller: Licensing: Creative Commons ShareAlike 4.0 International - https://creativecommons.org/licenses/by-sa/4.0
